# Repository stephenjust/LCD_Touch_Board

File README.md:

# 5-inch LCD / Multitouch Board
Drive an LCD with a multitouch panel using a
[PIC18F14K50](http://ww1.microchip.com/downloads/en/DeviceDoc/41350E.pdf)
and custom PCB!

*The code and CAD files for this project are incomplete, as the
project is under active development. If you have any questions,
please do not hesitate to contact the author.* This project began
in 2013 and has slowly been developed to where it is today in the
free time of the developer as a means to learn more about hardware
design. As such, it is not recommended that this project be used
as a model for commercial work and that developers exercise a
measured amount of caution when using this project.

The schematic and circuit board for this project was designed with
[Eagle 6.6.0](http://www.cadsoftusa.com/eagle-pcb-design-software/about-eagle/).
The board is small enough to be opened with the free version of
Eagle, and only uses two PCB layers. The circuit board can be
purchased from [OSHPark](http://www.oshpark.com) for about $30 USD
for 3 boards.

Assembling this project for yourself is no small task. The project
consists of a very wide range of components, ranging from ordering
custom circuit boards, ordering parts, soldering all of the surface
mount components to the board, and then programming the
microcontroller and eeprom on the board.

Once everything is assembled and running, you should have a small
[800x480 LCD](http://www.newhavendisplay.com/specs/NHD-5.0-800480TF-ATXI-CTP.pdf) 
available via an HDMI or DVI port, and a 5-point touch surface with
which to interact with it.

This project makes use of a [TPS61165](http://www.ti.com/product/tps61165)
LED backlight driver. This is sufficient to drive the backlight
in the LCD panel, and supports dimming via a 1-wire interface or
through PWM.

Please note that this design does not support HDCP, as it uses a
DVI display chip, the [TFP401A](http://www.ti.com/product/tfp401a).
If youi would like to modify this design to support HDCP, you
could build it around the TFP501 instead.

## Latest Schematic

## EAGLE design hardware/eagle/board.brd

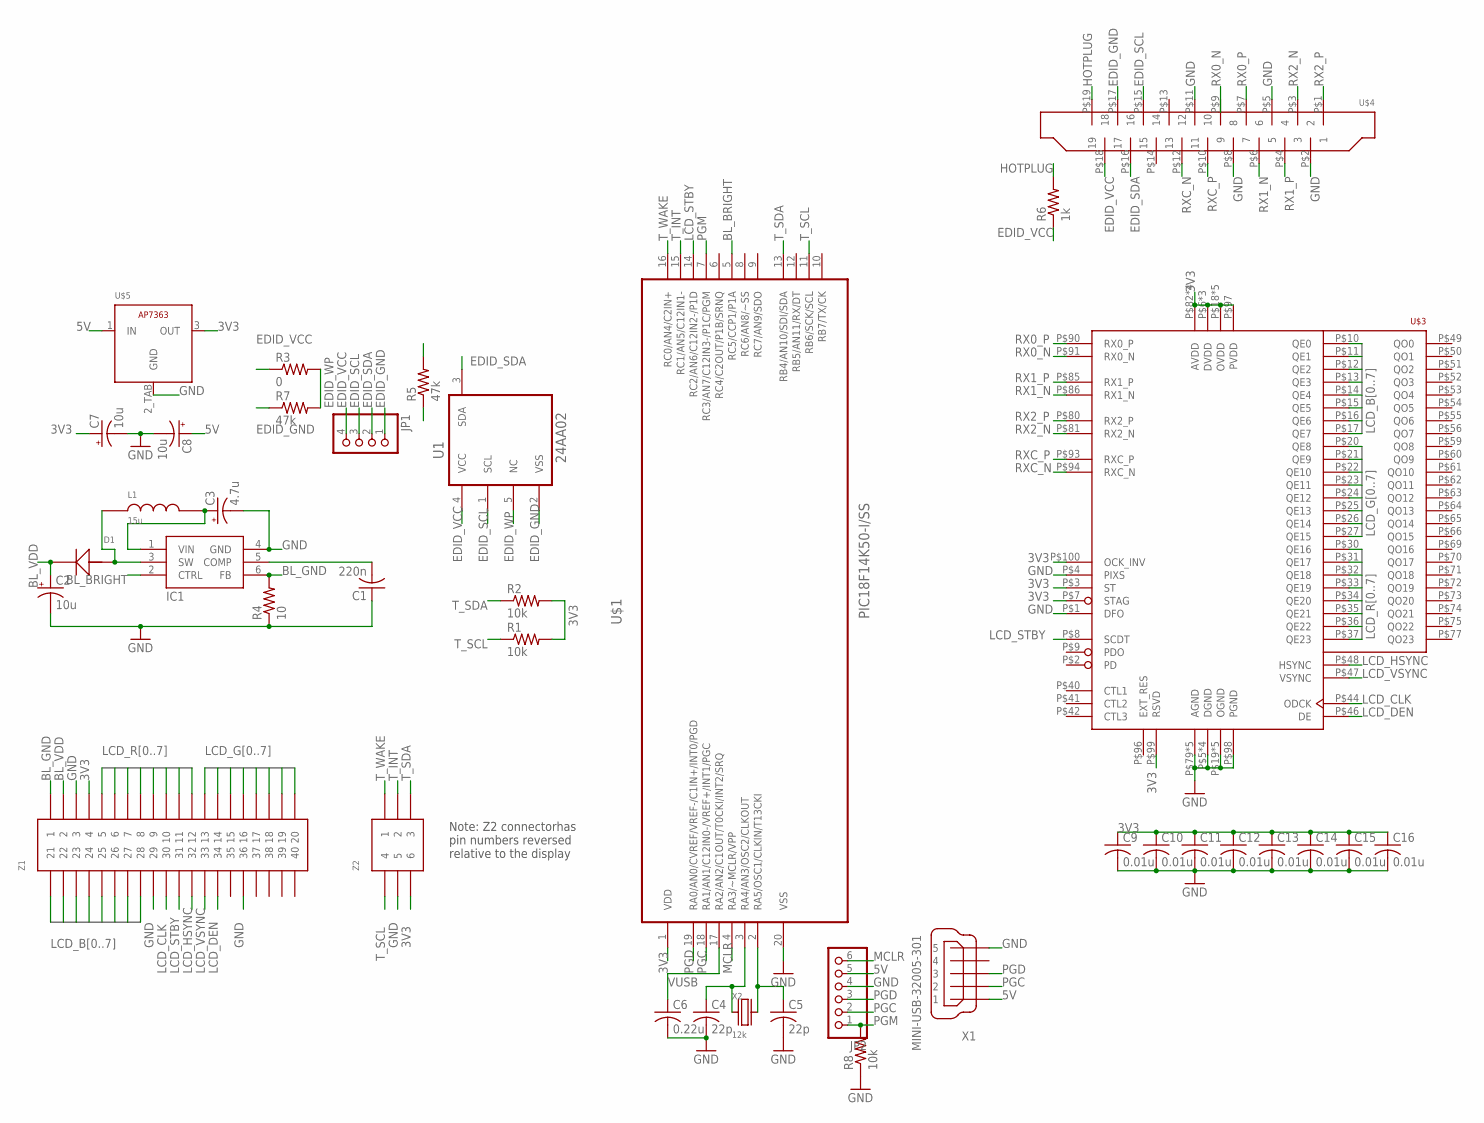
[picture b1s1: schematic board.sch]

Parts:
C1: 220n; C1206
C2, C7, C8: 10u; PANASONIC_B
C3: 4.7u; PANASONIC_B
C4, C5: 22p; C1206K
C6: 0.22u; C1206K
C9, C10, C11, C12, C13, C14, C15, C16: 0.01u; C0805
D1: MBR0540; SOD123
IC1: TPS61165; SOT-23-6
JP1: PINHD-1X4/90; 1X04/90
JP2: PINHD-1X6; 1X06
L1: 15u; 0520CDMCDS
R1, R2, R8: 10k; R1206
R3: 0; R0805
R4: 10; R0805
R5, R7: 47k; R1206
R6: 1k; R1206
U1: 24AA02; SOT95P270X145-5N
U$1: PIC18F14K50-I/SS; SOP65P780X200-20N
U$3: TFP401; PQFP-100
U$4: HDMI-RCPT; HDMI-RA-SMD
U$5: AP7363TO252; TO252
X1: MINI-USB-32005-301; 32005-301
X2: 12k; CTS-445
Z1: 62684-401100ALF
Z2: 84952-6

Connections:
3V3: C7.+, C9.1, C10.1, C11.1, C12.1, C13.1, C14.1, C15.1, C16.1, R1.2, R2.2, U$1.1 (VDD), U$3.P$3 (ST), U$3.P$6 (DVDD), U$3.P$7 (STAG), U$3.P$18 (OVDD), U$3.P$29 (OVDD), U$3.P$38 (DVDD), U$3.P$43 (OVDD), U$3.P$57 (OVDD), U$3.P$67 (DVDD), U$3.P$78 (OVDD), U$3.P$82 (AVDD), U$3.P$84 (AVDD), U$3.P$88 (AVDD), U$3.P$95 (AVDD), U$3.P$97 (PVDD), U$3.P$99 (RSVD), U$3.P$100 (OCK_INV), U$5.3 (OUT), Z1.4, Z2.6
5V: C3.+, C8.+, IC1.1 (VIN), JP2.5, L1.P$2, U$5.1 (IN), X1.1
BL_BRIGHT: IC1.2 (CTRL), U$1.5 (RC5/CCP1/P1A)
BL_COMP: C1.2, IC1.5 (COMP)
BL_GND: IC1.6 (FB), R4.2, Z1.1
BL_SW: D1.A, IC1.3 (SW), L1.P$1
BL_VDD: C2.+, D1.K, Z1.2
EDID_GND: JP1.1, R7.1, U1.2 (VSS), U$4.P$17 (17)
EDID_SCL: JP1.3, R5.2, U1.1 (SCL), U$4.P$15 (15)
EDID_SDA: JP1.2, U1.3 (SDA), U$4.P$16 (16)
EDID_VCC: JP1.4, R3.1, R5.1, R6.1, U1.4 (VCC), U$4.P$18 (18)
EDID_WP: R3.2, R7.2, U1.5 (NC)
GND: C1.1, C2.-, C3.-, C4.2, C5.2, C6.2, C7.-, C8.-, C9.2, C10.2, C11.2, C12.2, C13.2, C14.2, C15.2, C16.2, IC1.4 (GND), JP2.4, R4.1, R8.1, U$1.20 (VSS), U$3.P$1 (DFO), U$3.P$4 (PIXS), U$3.P$5 (DGND), U$3.P$19 (OGND), U$3.P$28 (OGND), U$3.P$39 (DGND), U$3.P$45 (OGND), U$3.P$58 (OGND), U$3.P$68 (DGND), U$3.P$76 (OGND), U$3.P$79 (AGND), U$3.P$83 (AGND), U$3.P$87 (AGND), U$3.P$89 (AGND), U$3.P$92 (AGND), U$3.P$98 (PGND), U$3.PAD (DGND), U$4.P$2 (2), U$4.P$5 (5), U$4.P$8 (8), U$4.P$11 (11), U$5.2_TAB (GND), X1.5, Z1.3, Z1.29, Z1.36, Z2.5
HOTPLUG: R6.2, U$4.P$19 (19)
LCD_B0: U$3.P$10 (QE0), Z1.21
LCD_B1: U$3.P$11 (QE1), Z1.22
LCD_B2: U$3.P$12 (QE2), Z1.23
LCD_B3: U$3.P$13 (QE3), Z1.24
LCD_B4: U$3.P$14 (QE4), Z1.25
LCD_B5: U$3.P$15 (QE5), Z1.26
LCD_B6: U$3.P$16 (QE6), Z1.27
LCD_B7: U$3.P$17 (QE7), Z1.28
LCD_CLK: U$3.P$44 (ODCK), Z1.30
LCD_DEN: U$3.P$46 (DE), Z1.34
LCD_G0: U$3.P$20 (QE8), Z1.13
LCD_G1: U$3.P$21 (QE9), Z1.14
LCD_G2: U$3.P$22 (QE10), Z1.15
LCD_G3: U$3.P$23 (QE11), Z1.16
LCD_G4: U$3.P$24 (QE12), Z1.17
LCD_G5: U$3.P$25 (QE13), Z1.18
LCD_G6: U$3.P$26 (QE14), Z1.19
LCD_G7: U$3.P$27 (QE15), Z1.20
LCD_HSYNC: U$3.P$48 (HSYNC), Z1.32
LCD_R0: U$3.P$30 (QE16), Z1.5
LCD_R1: U$3.P$31 (QE17), Z1.6
LCD_R2: U$3.P$32 (QE18), Z1.7
LCD_R3: U$3.P$33 (QE19), Z1.8
LCD_R4: U$3.P$34 (QE20), Z1.9
LCD_R5: U$3.P$35 (QE21), Z1.10
LCD_R6: U$3.P$36 (QE22), Z1.11
LCD_R7: U$3.P$37 (QE23), Z1.12
LCD_STBY: U$1.14 (RC2/AN6/C12IN2-/P1D), U$3.P$8 (SCDT), Z1.31
LCD_VSYNC: U$3.P$47 (VSYNC), Z1.33
MCLR: JP2.6, U$1.4 (RA3/~MCLR/VPP)
unnamed: C4.1, U$1.3 (RA4/AN3/OSC2/CLKOUT), X2.X1
unnamed: C5.1, U$1.2 (RA5/OSC1/CLKIN/T13CKI), X2.X2
PGC: JP2.2, U$1.18 (RA1/AN1/C12IN0-/VREF+/INT1/PGC), X1.2
PGD: JP2.3, U$1.19 (RA0/AN0/CVREF/VREF-/C1IN+/INT0/PGD), X1.3
PGM: JP2.1, R8.2, U$1.7 (RC3/AN7/C12IN3-/P1C/PGM)
RX0_N: U$3.P$91 (RX0_N), U$4.P$9 (9)
RX0_P: U$3.P$90 (RX0_P), U$4.P$7 (7)
RX1_N: U$3.P$86 (RX1_N), U$4.P$6 (6)
RX1_P: U$3.P$85 (RX1_P), U$4.P$4 (4)
RX2_N: U$3.P$81 (RX2_N), U$4.P$3 (3)
RX2_P: U$3.P$80 (RX2_P), U$4.P$1 (1)
RXC_N: U$3.P$94 (RXC_N), U$4.P$12 (12)
RXC_P: U$3.P$93 (RXC_P), U$4.P$10 (10)
T_INT: U$1.15 (RC1/AN5/C12IN1-), Z2.2
T_SCL: R1.1, U$1.11 (RB6/SCK/SCL), Z2.4
T_SDA: R2.1, U$1.13 (RB4/AN10/SDI/SDA), Z2.3
T_WAKE: U$1.16 (RC0/AN4/C2IN+), Z2.1
VUSB: C6.1, U$1.17 (RA2/AN2/C1OUT/T0CKI/INT2/SRQ)

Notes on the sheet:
Note: Z2 connectorhas pin numbers reversed relative to the display

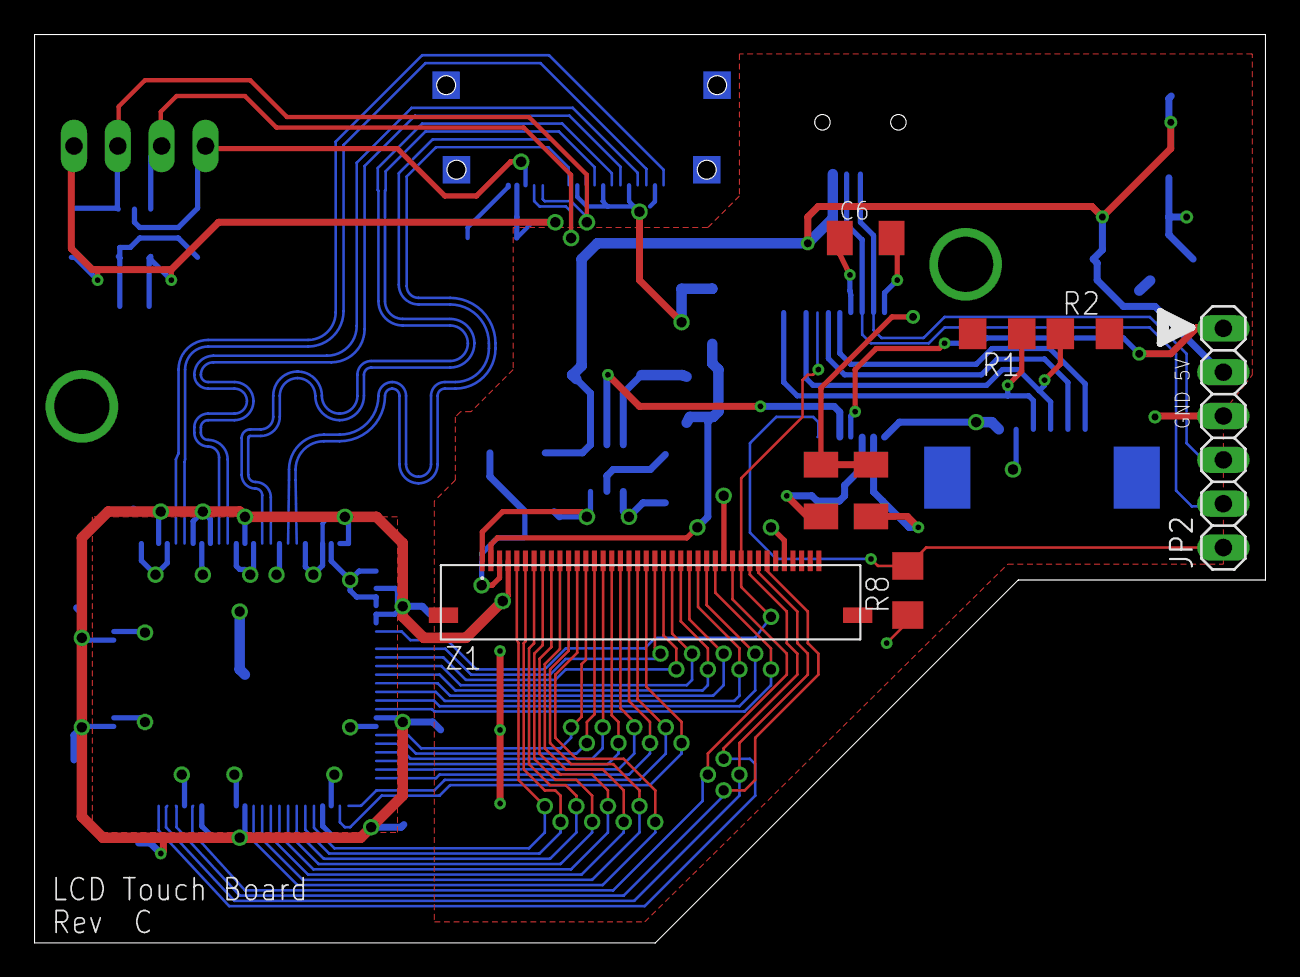
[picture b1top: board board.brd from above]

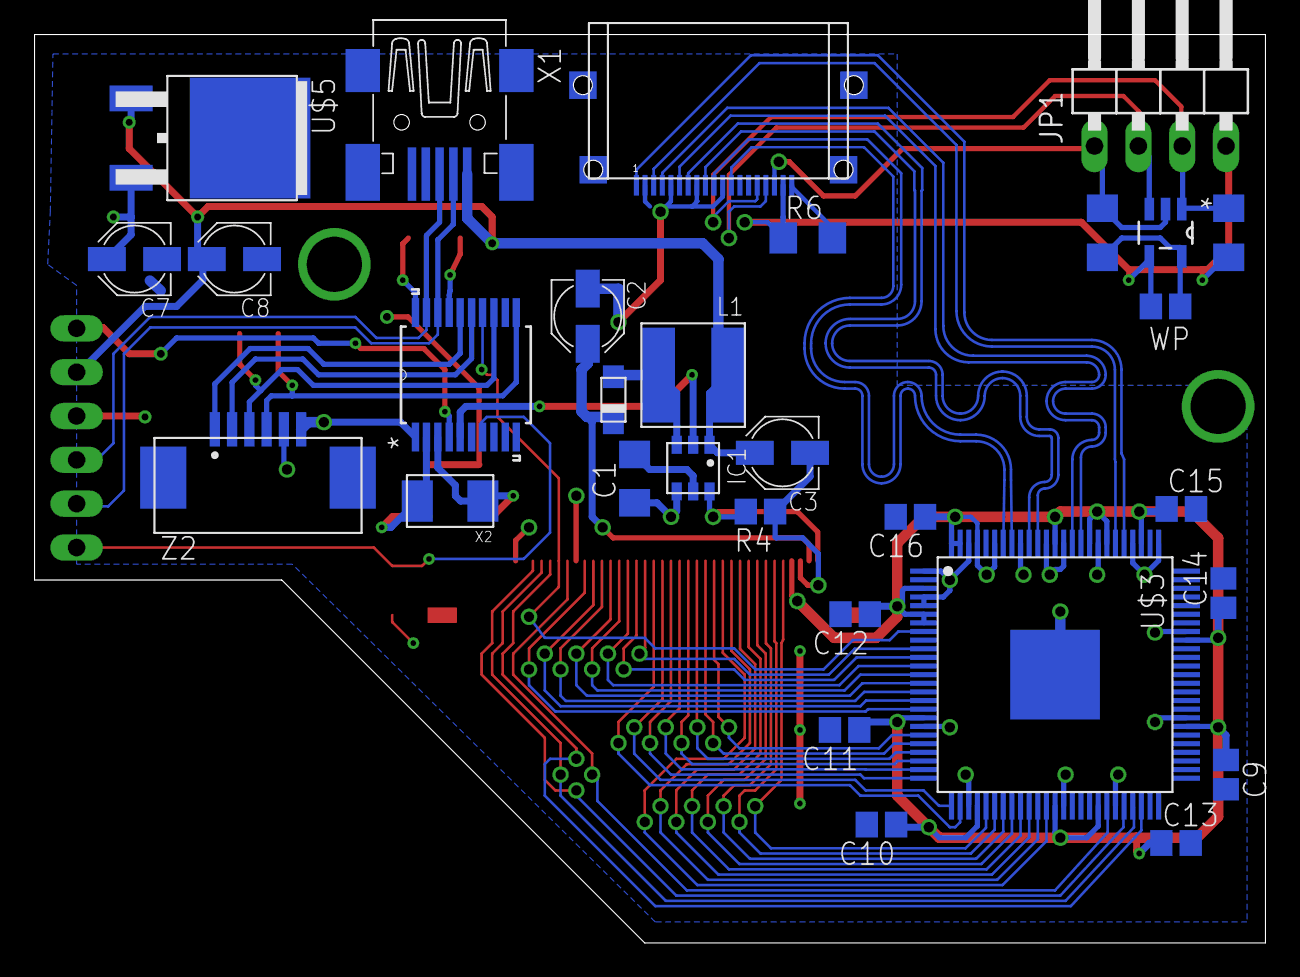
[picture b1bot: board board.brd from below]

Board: 2 copper layers, 71.3 x 52.6 mm, 38 parts (30 on the bottom side), 62 nets.

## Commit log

2015-03-15 Add .gitignore
2015-03-15 Add initial backlight code
2015-03-15 Add project files
2015-03-15 Backlight works now
    I had forgotten to set the configuration values, so an incorrect
    clock source was being used.
2015-03-16 Add M-Stack USB library with modifications
    HID descriptors have been modified to match the hardware attached.
    The M-Stack library was also modified to compile with the
    PIC18F14K50.
2015-03-16 Update project files
2015-03-16 Add Eagle files for this design.
    This includes the project files, schematic, board, and custom
    part libraries.
2015-03-16 Add image of the board schematic
2015-03-16 Create README.md
    Added a README file to talk about the project.
2015-03-18 Attempt to enable USB device based on M-stack ex.
    This did not seem to work, but checking it in
    anyways.
2015-03-18 Add I2C files from old project.
2015-03-18 Add touchpanel code files
    These files are based on the old project, but
    modified to make use of m-stack instead of the
    old PIC demo code.
2015-03-19 Remove m-stack, use Microchip's USB HID demo
    m-stack wasn't compatible with my device, but
    the existing Microchip demo code was. So far this
    code is at least properly enabling the usb tranceiver.
2015-03-19 Update code files to use the new USB stack
2015-03-20 Get USB into a state where it will talk to a PC
    Interrupts with the touch panel are conflicting with USB.
    Will investigate that...
2015-03-20 Remove unused files
2015-03-20 Attempt to fix touch panel interrupts.
    Still not working, not entirely sure why...
2015-03-22 Sending touch data over USB works now!
    Exact touch details are not yet correct, but this is a good start.
    Data is being transferred from the touch panel to a computer.
2015-03-24 Fix USB descriptors
    USB analyzers inform me that the old descriptor was not correct.
    The new version should be better than the old one.
    Also enabled the backlight.
2015-03-25 Fix byte ordering in USB report and touchpad data
    Lots of byte-ordering issues are fixed now. "In Range"
    field had to be added to match Windows digitizer spec.
    Touch seems to work now.
2015-03-28 Added code to write EDID for display
    This code is from Adafruit's tutorial for their TFP401-based design.
    See
    https://learn.adafruit.com/adafruit-tfp401-hdmi-slash-dvi-decoder-to-40-pin-ttl-display/editing-the-edid
2015-03-28 Update Eagle files
    Tweaked design to shrink the PCB, remove
    backlight buttons, and removed the diode
    on MCLR for the microcontroller.
2015-03-29 Clean up code a bit
2015-03-29 Added library for cheaper voltage reg
2015-03-29 Shrank circuit again.
    Circuit board is smaller now, and also has the proper
    wiring for low voltage programming. The missing resistor
    was causing unexpected reboots of the device.
2015-03-29 Updated schematic image
